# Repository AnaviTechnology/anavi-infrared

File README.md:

# ANAVI Infrared pHAT

ANAVI Infrared pHAT is an open source hardware Raspberry Pi pHAT (add-on board) for rapid prototyping of Internet of Things (IoT) powered by free and open source software. It features:

* 2x IR transmitters
* IR receiver (IR photo sensor)
* Slots for up to 3 plug and play I2C sensors for temperature, barometric pressure, humidity and light
* UART (Universal asynchronous receiver/transmitter) pins for debugging

ANAVI Infrared pHAT is available at [CrowdSupply](https://www.crowdsupply.com/anavi-technology/infrared-phat).

# License

The project is released under the [Creative Commons Attribution-ShareAlike 4.0 International (CC BY-SA 4.0)](https://creativecommons.org/licenses/by-sa/4.0/).

Note: This is a human-readable summary of (and not a substitute for) the [license](https://creativecommons.org/licenses/by-sa/4.0/legalcode).

You are free to:

Share — copy and redistribute the material in any medium or format Adapt — remix, transform, and build upon the material for any purpose, even commercially. The licensor cannot revoke these freedoms as long as you follow the license terms. Under the following terms:

Attribution — You must give appropriate credit, provide a link to the license, and indicate if changes were made. You may do so in any reasonable manner, but not in any way that suggests the licensor endorses you or your use. ShareAlike — If you remix, transform, or build upon the material, you must distribute your contributions under the same license as the original. No additional restrictions — You may not apply legal terms or technological measures that legally restrict others from doing anything the license permits. Notices:

You do not have to comply with the license for elements of the material in the public domain or where your use is permitted by an applicable exception or limitation. No warranties are given. The license may not give you all of the permissions necessary for your intended use. For example, other rights such as publicity, privacy, or moral rights may limit how you use the material.

You will have to provide a link to the original creator of the project http://www.anavi.technology on any documentation or website.

Credit can be attributed through a link to the creator website: http://www.anavi.technology

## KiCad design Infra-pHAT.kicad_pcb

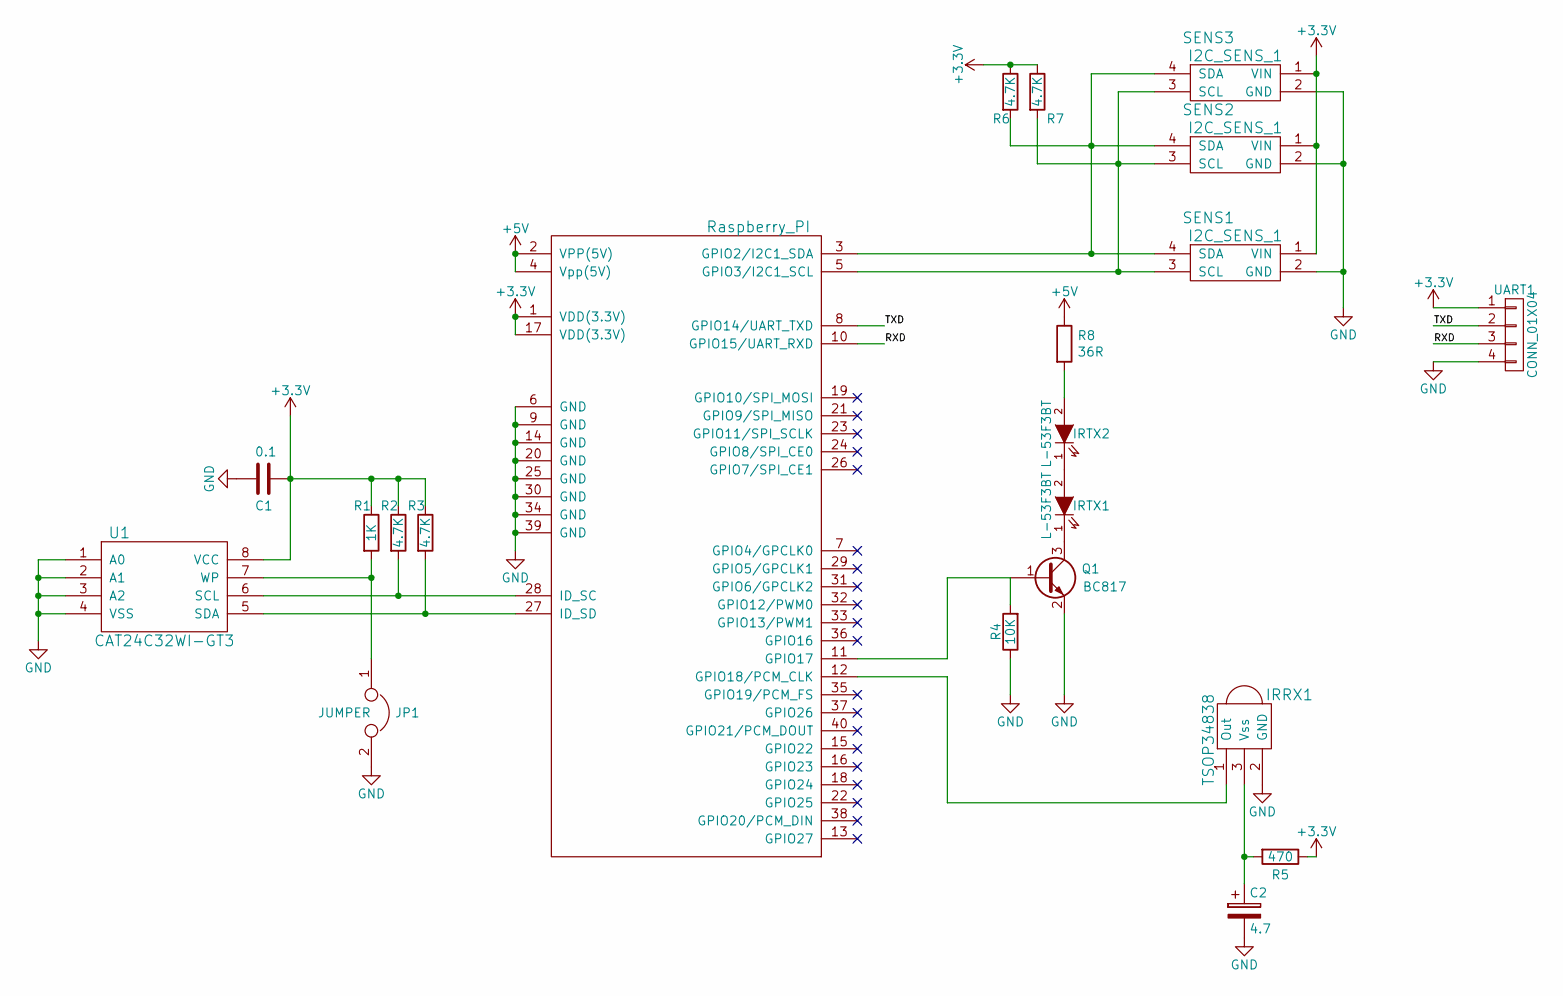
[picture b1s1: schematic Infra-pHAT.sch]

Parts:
C1: 0.1; C_0603_HandSoldering
C2: 4.7; C_0805_HandSoldering
IRRX1: TSOP34838; TSOP38X
IRTX1, IRTX2: L-53F3BT; LED-5MM
JP1: JUMPER; Pin_Header_Straight_1x02
Q1: BC817; SOT-23
R1: 1K; R_0603_HandSoldering
R2, R3, R6, R7: 4.7K; R_0603_HandSoldering
R4: 10K; R_0603_HandSoldering
R5: 470; R_0603_HandSoldering
R8: 36R; R_0603_HandSoldering
RASP_CONN1: Raspberry_PI; Pin_Header_Straight_2x20
SENS1, SENS2, SENS3: I2C_SENS_1; Pin_Header_Straight_1x04
U1: CAT24C32WI-GT3; DIP-8_W7.62mm
UART1: CONN_01X04; Pin_Header_Straight_1x04

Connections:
+3V3: C1.1, R1.1, R2.1, R3.1, R5.1, R6.1, R7.1, RASP_CONN1.1 (VDD(3.3V)), RASP_CONN1.17 (VDD(3.3V)), SENS1.1 (VIN), SENS2.1 (VIN), SENS3.1 (VIN), U1.8 (VCC), UART1.1; also elsewhere on the board
+5V: R8.1, RASP_CONN1.2 (VPP(5V)), RASP_CONN1.4 (Vpp(5V))
/RXD: RASP_CONN1.10 (GPIO15/UART_RXD), UART1.3; also elsewhere on the board
/TXD: RASP_CONN1.8 (GPIO14/UART_TXD), UART1.2; also elsewhere on the board
GND: C1.2, C2.2, IRRX1.2 (GND), JP1.2, Q1.2 (E), R4.1, RASP_CONN1.6 (GND), RASP_CONN1.9 (GND), RASP_CONN1.14 (GND), RASP_CONN1.20 (GND), RASP_CONN1.25 (GND), RASP_CONN1.30 (GND), RASP_CONN1.34 (GND), RASP_CONN1.39 (GND), SENS1.2 (GND), SENS2.2 (GND), SENS3.2 (GND), U1.1 (A0), U1.2 (A1), U1.3 (A2), U1.4 (VSS), UART1.4; also elsewhere on the board
unnamed: C2.1, IRRX1.3 (Vss), R5.2
unnamed: IRRX1.1 (Out), RASP_CONN1.12 (GPIO18/PCM_CLK)
unnamed: IRTX1.1 (K), Q1.3 (C)
unnamed: IRTX1.2 (A), IRTX2.1 (K)
unnamed: IRTX2.2 (A), R8.2
unnamed: JP1.1, R1.2, U1.7 (WP)
unnamed: Q1.1 (B), R4.2, RASP_CONN1.11 (GPIO17)
unnamed: R2.2, RASP_CONN1.28 (ID_SC), U1.6 (SCL)
unnamed: R3.2, RASP_CONN1.27 (ID_SD), U1.5 (SDA)
unnamed: R6.2, RASP_CONN1.3 (GPIO2/I2C1_SDA), SENS1.4 (SDA), SENS2.4 (SDA), SENS3.4 (SDA)
unnamed: R7.2, RASP_CONN1.5 (GPIO3/I2C1_SCL), SENS1.3 (SCL), SENS2.3 (SCL), SENS3.3 (SCL)

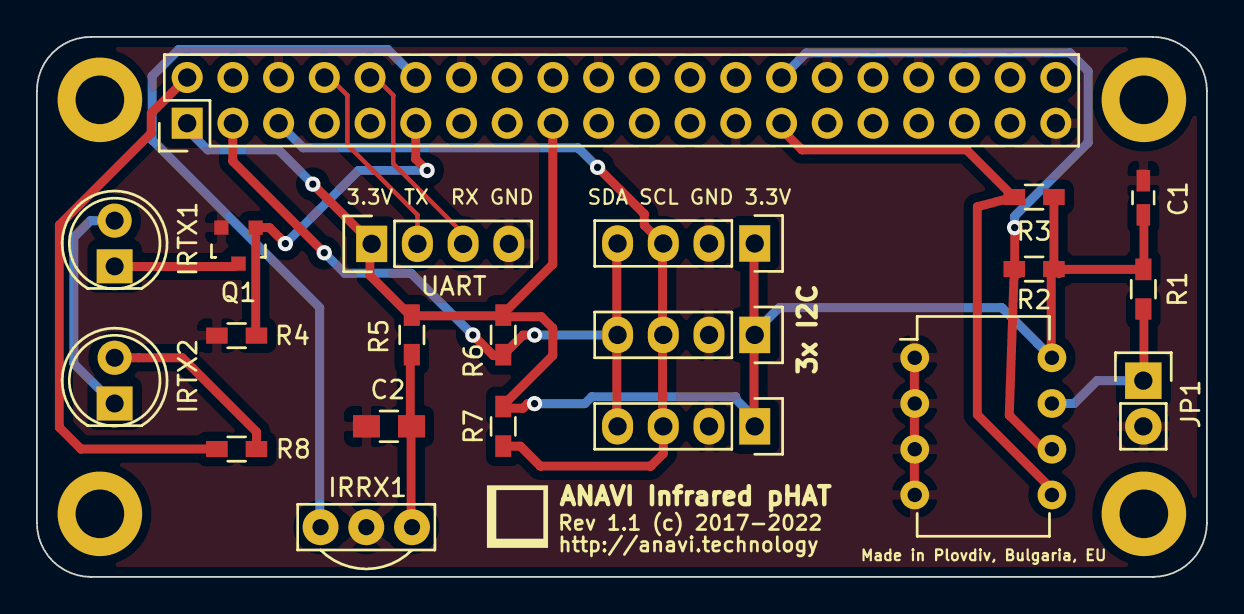
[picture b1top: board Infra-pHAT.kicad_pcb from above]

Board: 2 copper layers, 65.0 x 30.0 mm, 25 parts (0 on the bottom side), 16 nets.

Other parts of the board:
REF1, REF2, REF3, REF4: MountingHole_2.7mm_M2.5_DIN965_Pad
UART: CONN_01X04; Pin_Header_Straight_1x04

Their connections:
+3V3: UART.1; also elsewhere on the board
/RXD: UART.3; also elsewhere on the board
/TXD: UART.2; also elsewhere on the board
GND: UART.4; also elsewhere on the board

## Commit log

2017-01-21 Infra-pHAT.kicad_pcb: Adjust positions
2017-01-21 README.md: Update information
2017-01-21 Infra-pHAT.kicad_pcb: Update settings
    Increase traces and vias.
2017-01-21 Infra-pHAT.kicad_pcb: Rearange components
2017-01-21 Infra-pHAT.kicad_pcb: Fix edge cuts
2017-01-21 Infra-pHAT.kicad_pcb: make space for tracing
2017-01-22 Infra-pHAT.kicad_pcb: Roteate UART
2017-01-22 Infra-pHAT.kicad_pcb: Route EEPROM
2017-01-22 Infra-pHAT.kicad_pcb: Route I2C slots
2017-01-22 Infra-pHAT.kicad_pcb: Route IR LED
2017-01-22 Infra-pHAT.kicad_pcb: Fix holes numbering
    Fix the numbering of the pads of the the mounting
    holes.
2017-01-22 Infra-pHAT.kicad_pcb: Route for IR RX
2017-01-22 Fix position of mounting holes and pin header
    Fix wiring of transistor for IR leds
2017-01-22 Add filled zone for front layer (GND net)
    Route RX/TX for UART connector
2017-01-22 Infra-pHAT.kicad_pcb: Update routing
2017-01-22 Infra-pHAT.kicad_pcb: Silkscreen text added
2017-01-22 Add logo and update tesxt on the silkscreen
2017-01-22 Infra-pHAT.kicad_pcb: Add revision number
2017-01-22 Infra-pHAT.kicad_pcb: Increase text size
2017-01-22 Update logo, texts and IRTX position
2017-01-23 Update name
2017-01-31 Infra-pHAT.kicad_pcb: Add assembly instructions
2017-02-18 Remove not relevant PDFs.
2018-03-25 README.md: CC BY-SA 4.0
    Switch license to CC BY-SA 4.0 because my newer
    open source hardware projects are with the same
    license.
2018-03-25 README.md: Update description
    Update description, fix project title and a link
    to CrowdSupply.
2018-12-10 Adding simple script to decode Toshiba AC controls
2018-12-10 Small fixes to ac-toshiba.py
2018-12-10 Adding small script to read IR packets.
2020-01-21 README.md: Fix typo
2022-04-20 Infra-pHAT.pro: remap symbols
    Remap KiCad symbols.
2022-04-22 Infra-pHAT.*: Add a current limiting resistor
    Add a current limiting resistor for the IR LEDs.
    Suggested-by: Norman Rasmussen <norman@rasmussen.co.za>
2022-04-25 Infra-pHAT.kicad_pcb: Update export rules
    Update configurations for exporting gerber and drill files.

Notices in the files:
Infra-pHAT.kicad_pcb:
Rev 1.1 (c) 2017-2022
